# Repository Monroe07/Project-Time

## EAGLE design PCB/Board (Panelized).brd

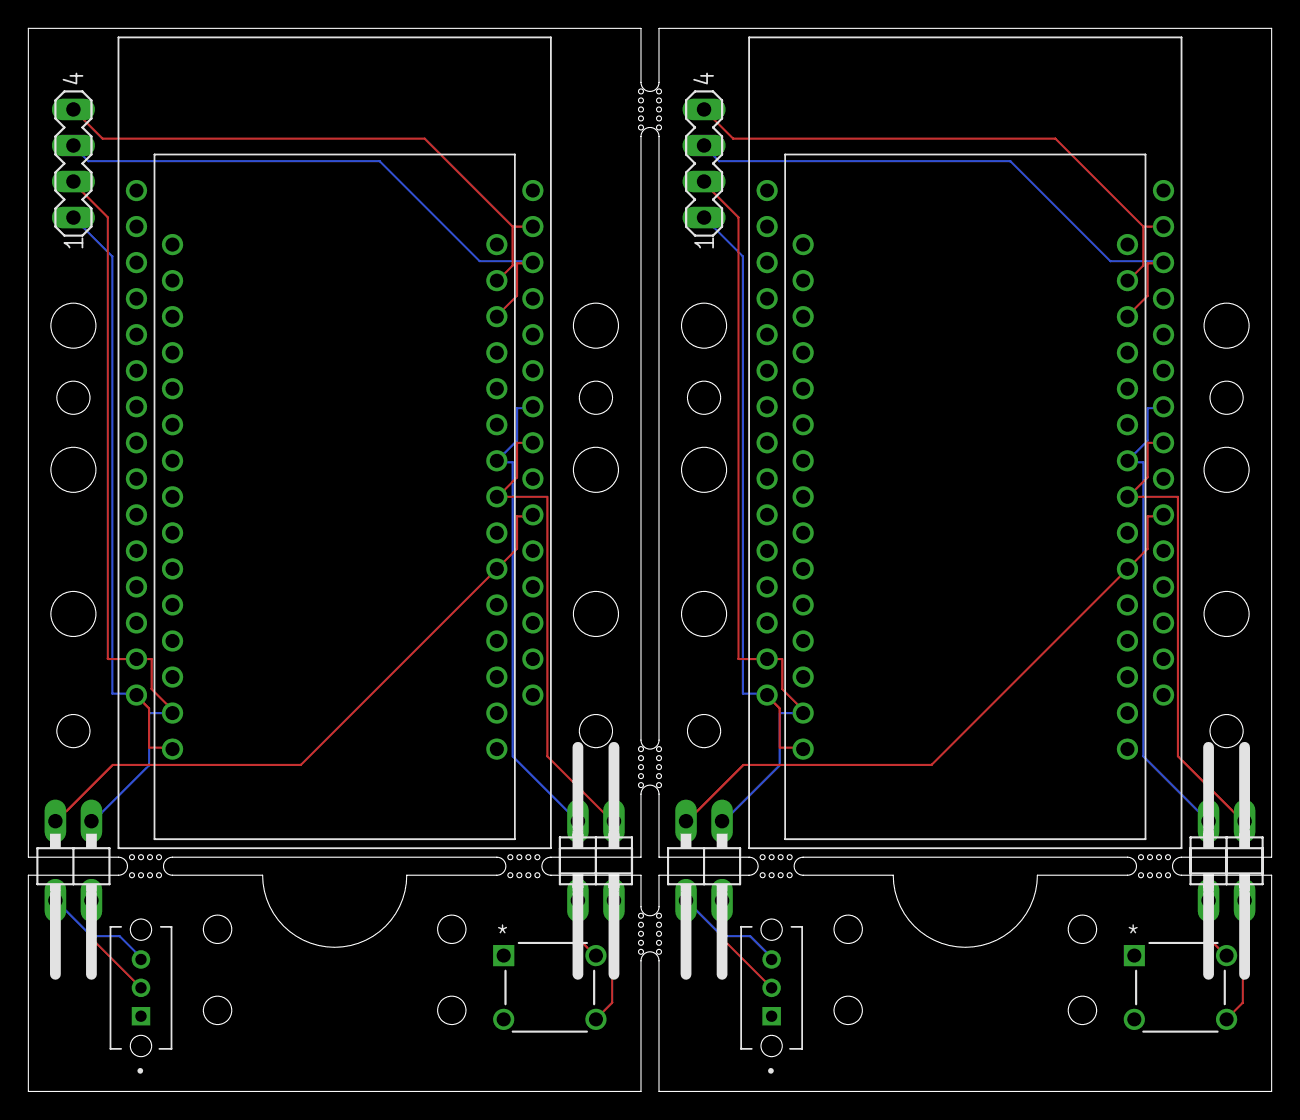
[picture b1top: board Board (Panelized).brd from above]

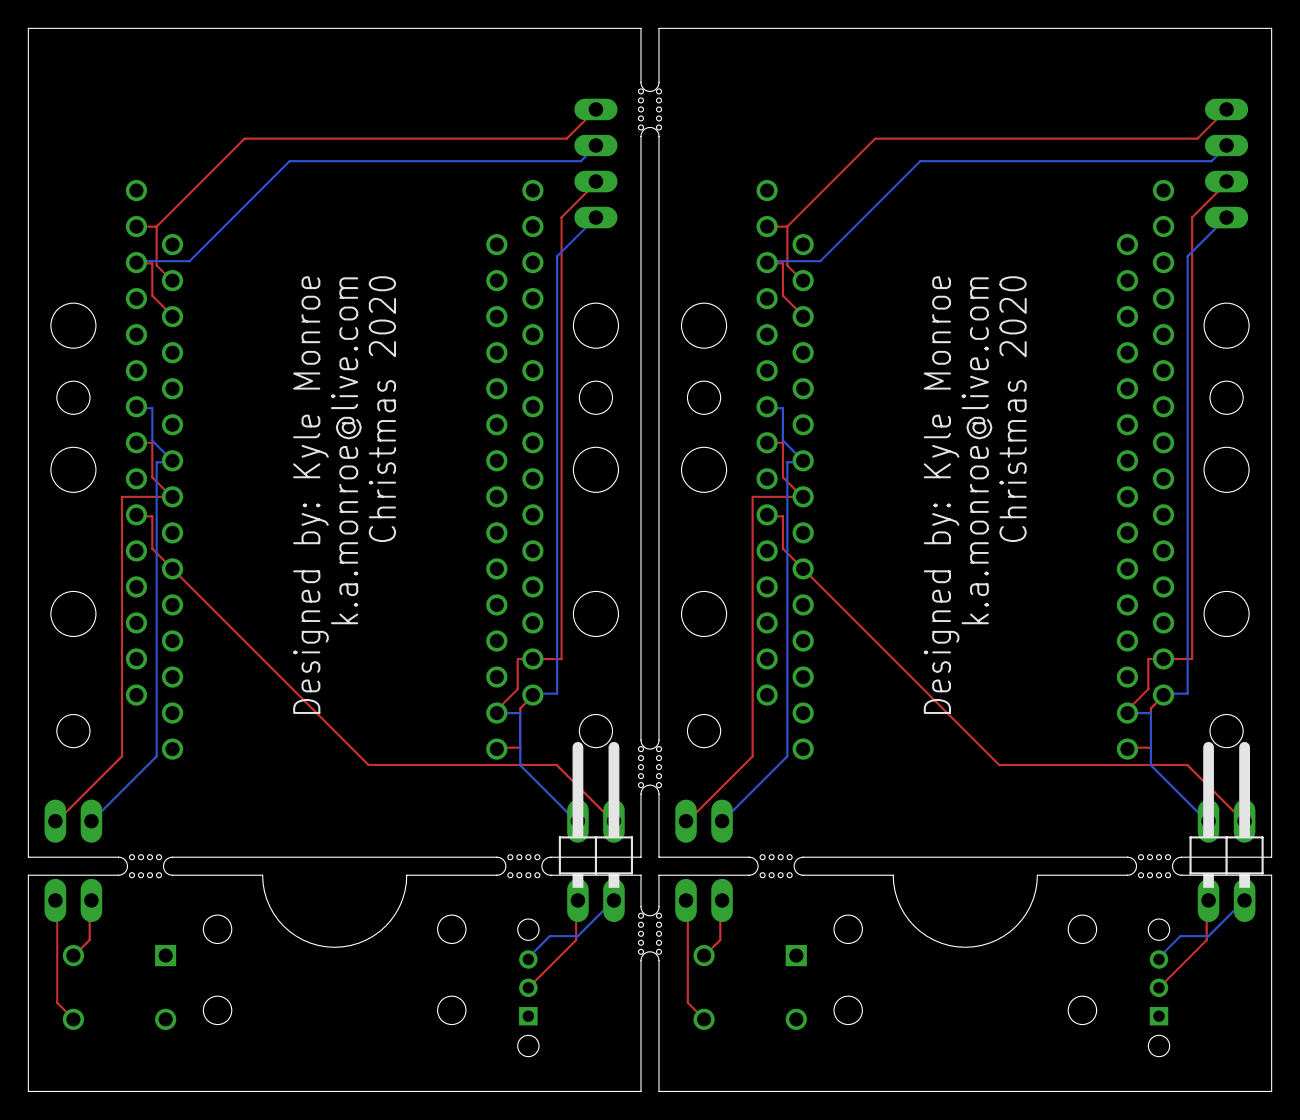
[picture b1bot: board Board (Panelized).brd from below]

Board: 2 copper layers, 87.6 x 74.9 mm, 18 parts (2 on the bottom side), 22 nets.

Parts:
JP1, JP2, JP3, JP4, JP5, JP6, JP7, JP8: 1X02/90
S1, S2: dstSwitch; SW_OS102011MS2QN1
SV1, SV2: MA04-1
SW1, SW2: configButton; SW4_1825910-B_TEC
U$1, U$3: ESP-12F(SMALL); ESP-12E(SMALL)
U$2, U$4: ESP-12F(LARGE); ESP-12E(LARGE)

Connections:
unnamed: JP1.1, U$1.GPIO14, U$2.GPIO14
unnamed: JP1.2, U$1.GND3, U$2.GND3
unnamed: JP7.2, U$3.GPIO13, U$4.GPIO13
unnamed: JP7.1, SV2.2, U$3.GND2, U$4.GND2
unnamed: JP3.2, U$1.GPIO13, U$2.GPIO13
unnamed: SV2.1, U$3.VIN, U$4.VIN
unnamed: SV2.3, U$3.GPIO4, U$4.GPIO4
unnamed: SV2.4, U$3.GPIO5, U$4.GPIO5
unnamed: JP8.1, S2.2
unnamed: JP8.2, S2.3
unnamed: JP6.1, SW2.2
unnamed: JP6.2, SW2.4
unnamed: JP3.1, SV1.2, U$1.GND2, U$2.GND2
unnamed: SV1.1, U$1.VIN, U$2.VIN
unnamed: JP5.1, U$3.GPIO14, U$4.GPIO14
unnamed: JP5.2, U$3.GND3, U$4.GND3
unnamed: SV1.3, U$1.GPIO4, U$2.GPIO4
unnamed: SV1.4, U$1.GPIO5, U$2.GPIO5
unnamed: JP4.1, S1.2
unnamed: JP4.2, S1.3
unnamed: JP2.1, SW1.2
unnamed: JP2.2, SW1.4

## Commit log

2024-08-26 Added Files for Case
2024-08-26 Added PCB Eagle and Cam Files

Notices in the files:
parts and their libraries:
COPYRIGHT: Copyright (C) 2016 Accelerated Designs. All rights reserved
